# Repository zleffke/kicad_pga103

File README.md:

# kicad_pga103
PGA-103 based low noise amplifier designs.

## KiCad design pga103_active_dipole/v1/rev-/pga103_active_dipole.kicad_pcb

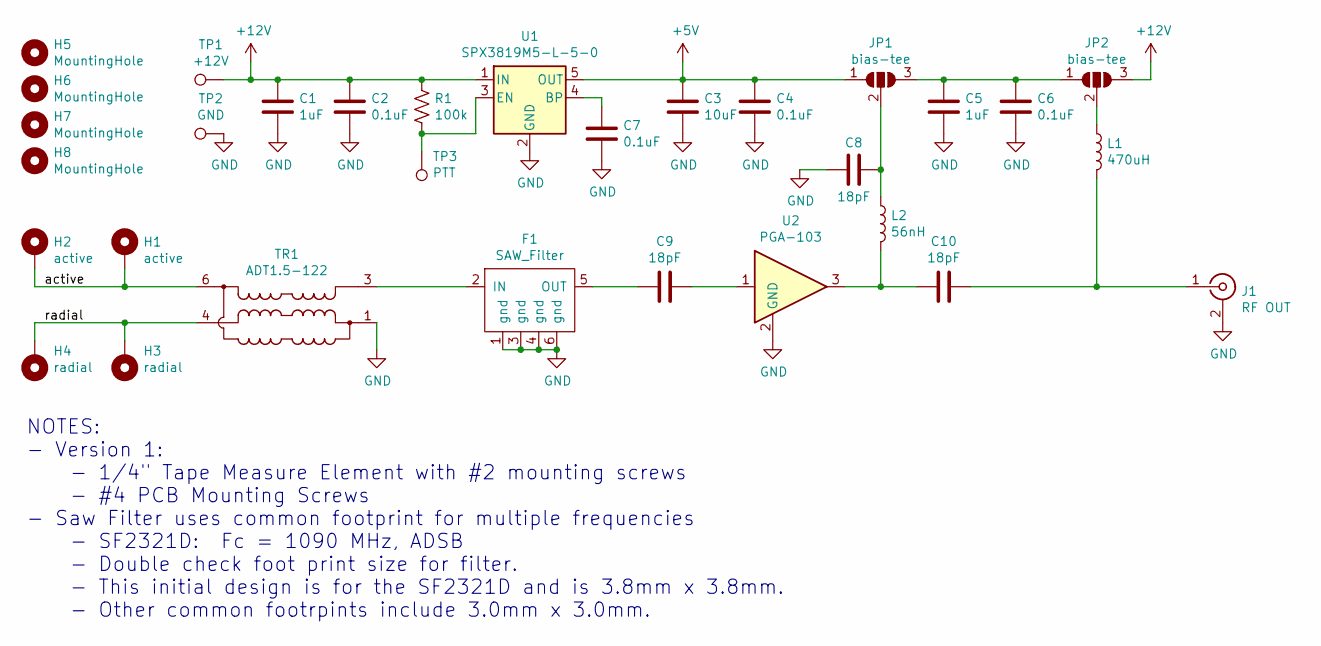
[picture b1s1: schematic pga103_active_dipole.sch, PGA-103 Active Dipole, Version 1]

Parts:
C1, C5: 1uF; 0805
C2, C4, C6, C7: 0.1uF; 0805
C3: 10uF; 0805
C8, C9, C10: 18pF; 0805
F1: SAW_Filter; SM3838-6_3.8mmx3.8mm
H1, H2: active; MountingHole_2.5mm_Pad_Via
H3, H4: radial; MountingHole_2.5mm_Pad_Via
H5, H6, H7, H8: MountingHole; MountingHole_3.2mm_M3
J1: RF OUT; SMA_Samtec_SMA-J-P-X-ST-EM1_EdgeMount
JP1, JP2: bias-tee; SolderJumper-3_P1.3mm_Open_RoundedPad1.0x1.5mm
L1: 470uH; 0805
L2: 56nH; 0805
R1: 100k; 0805
TP1: +12V; TestPoint_Pad_2.0x2.0mm
TP2: GND; TestPoint_Pad_2.0x2.0mm
TP3: PTT; TestPoint_Pad_2.0x2.0mm
TR1: ADT1.5-122; Mini-Circuits_CD542_H2.84mm
U1: SPX3819M5-L-5-0; SOT-23-5
U2: PGA-103; SOT-89-3

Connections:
+5V: C3.1, C4.1, JP1.1 (A), U1.5 (OUT)
+12V: C1.1, C2.1, JP2.3 (B), R1.1, TP1.1, U1.1 (IN)
/active: H1.1, H2.1, TR1.6
/radial: H3.1, H4.1, TR1.4
GND: C1.2, C2.2, C3.2, C4.2, C5.2, C6.2, C7.2, C8.1, F1.1 (gnd), F1.3 (gnd), F1.4 (gnd), F1.6 (gnd), J1.2 (Ext), TP2.1, TR1.1, TR1.2, U1.2 (GND), U2.2 (GND)
unnamed: C5.1, C6.1, JP1.3 (B), JP2.1 (A)
unnamed: C7.1, U1.4 (BP)
unnamed: C8.2, JP1.2 (C), L2.1
unnamed: C9.1, U2.1
unnamed: C9.2, F1.5 (OUT)
unnamed: C10.1, J1.1 (In), L1.2
unnamed: C10.2, L2.2, U2.3
unnamed: F1.2 (IN), TR1.3
unnamed: JP2.2 (C), L1.1
unnamed: R1.2, TP3.1, U1.3 (EN)

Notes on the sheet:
NOTES: - Version 1: - 1/4" Tape Measure Element with #2 mounting screws - #4 PCB Mounting Screws - Saw Filter uses common footprint for multiple frequencies - SF2321D: Fc = 1090 MHz, ADSB - Double check foot print size for filter. - This initial design is for the SF2321D and is 3.8mm x 3.8mm. - Oth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

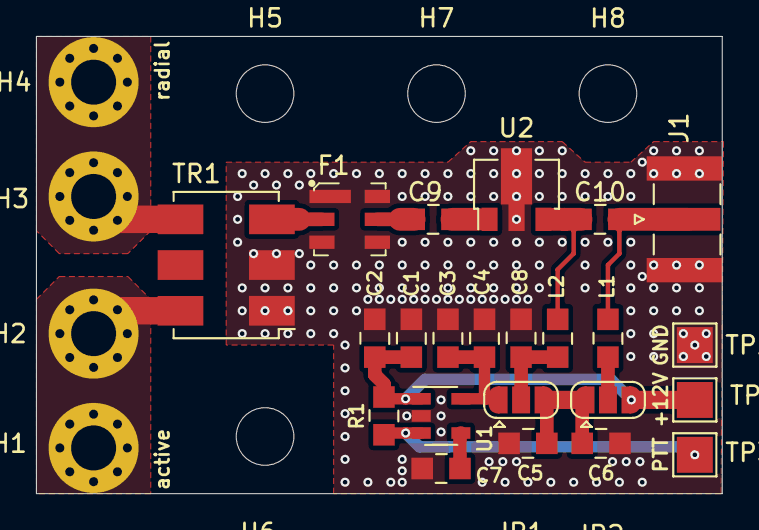
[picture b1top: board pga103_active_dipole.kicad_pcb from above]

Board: 2 copper layers, 38.1 x 25.4 mm, 31 parts (0 on the bottom side), 15 nets.

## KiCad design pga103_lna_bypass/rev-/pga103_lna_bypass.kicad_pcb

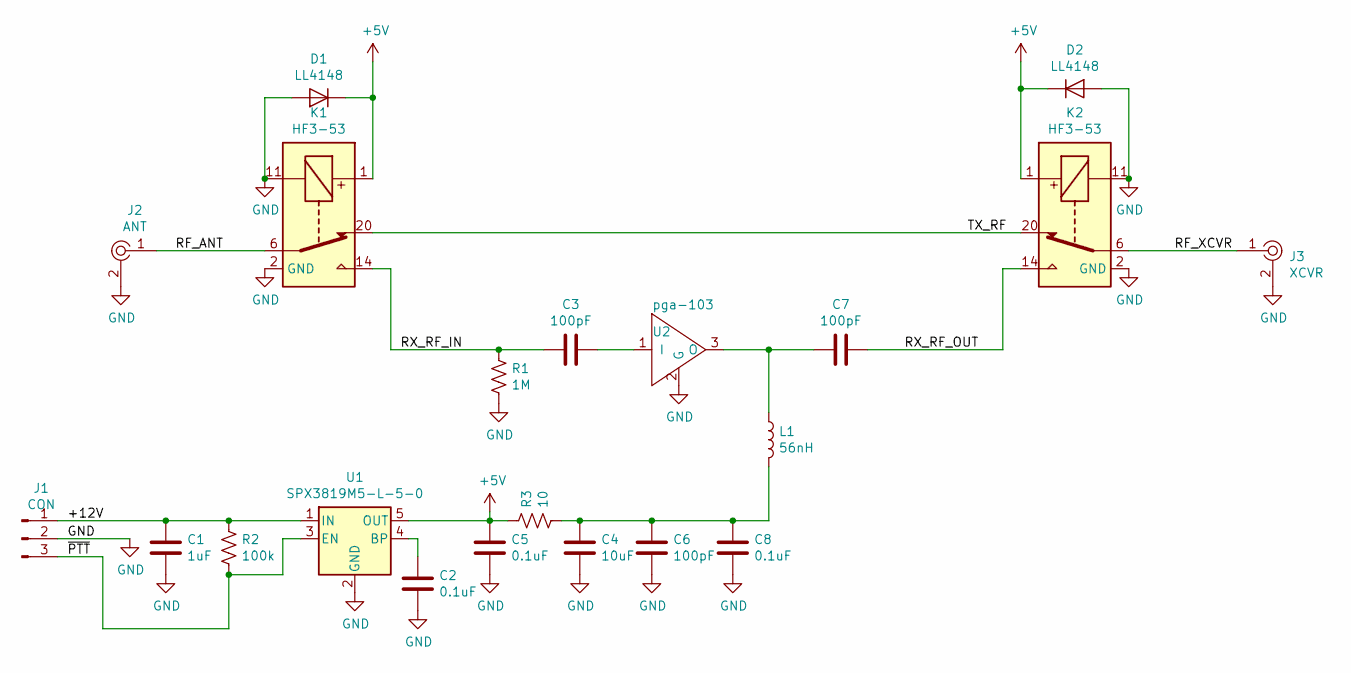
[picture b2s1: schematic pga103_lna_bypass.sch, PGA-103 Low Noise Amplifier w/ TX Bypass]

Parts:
C1: 1uF; 0805
C2, C5, C8: 0.1uF; 0805
C3, C6, C7: 100pF; 0805
C4: 10uF; 0805
D1, D2: LL4148; D_MiniMELF
J1: CON; PinHeader_1x03_P2.54mm_Vertical
J2: ANT; RF_SMA_BoardEdge_142-0701-801; MPN 142-0701-801; Digi-Key_PN J502-ND
J3: XCVR; RF_SMA_BoardEdge_142-0701-801; MPN 142-0701-801; Digi-Key_PN J502-ND
K1, K2: HF3-53; Relay_SPDT_AXICOM_HF3Series_50ohms_Pitch1.27mm
L1: 56nH; 0805
R1: 1M; 0805
R2: 100k; 0805
R3: 10; 0805
U1: SPX3819M5-L-5-0; SOT-23-5
U2: pga-103; SOT-89-3

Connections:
+5V: C5.2, D1.1 (K), D2.1 (K), K1.1, K2.1, R3.2, U1.5 (OUT)
/+12V: C1.2, J1.1, R2.2, U1.1 (IN)
/RF_ANT: J2.1, K1.6
/RF_XCVR: J3.1, K2.6
/RX_RF_IN: C3.2, K1.14, R1.2
/RX_RF_OUT: C7.1, K2.14
/TX_RF: K1.20, K2.20
/~PTT: J1.3, R2.1, U1.3 (EN)
GND: C1.1, C2.1, C4.1, C5.1, C6.1, C8.1, D1.2 (A), D2.2 (A), J1.2, J2.2, J3.2, K1.2 (GND), K1.5 (GND), K1.7 (GND), K1.10 (GND), K1.11, K1.12 (GND), K1.13 (GND), K1.15 (GND), K1.17 (GND), K1.19 (GND), K1.21 (GND), K1.22 (GND), K2.2 (GND), K2.5 (GND), K2.7 (GND), K2.10 (GND), K2.11, K2.12 (GND), K2.13 (GND), K2.15 (GND), K2.17 (GND), K2.19 (GND), K2.21 (GND), K2.22 (GND), R1.1, U1.2 (GND), U2.2 (G)
unnamed: C2.2, U1.4 (BP)
unnamed: C3.1, U2.1 (I)
unnamed: C4.2, C6.2, C8.2, L1.2, R3.1
unnamed: C7.2, L1.1, U2.3 (O)

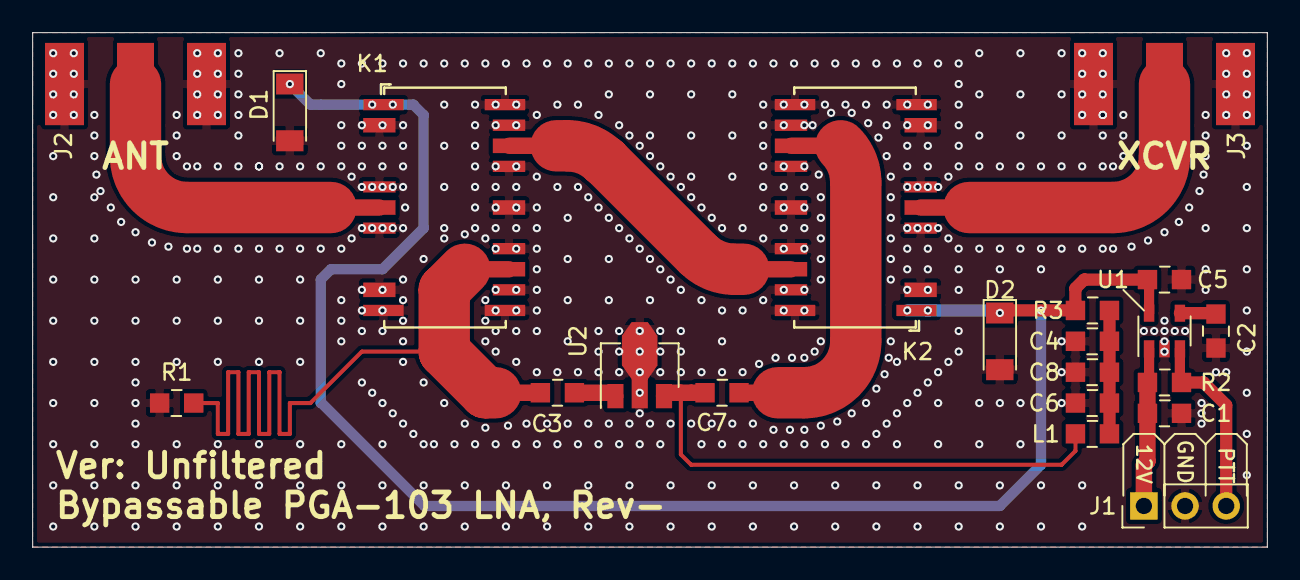
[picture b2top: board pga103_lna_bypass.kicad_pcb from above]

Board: 2 copper layers, 76.2 x 31.8 mm, 21 parts (0 on the bottom side), 13 nets.

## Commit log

2020-11-23 mass commit....not sure the status but might be close to done
2020-12-17 pga-103 active dipole for ADSB reception. This commit submitted to Osh Park.
2021-01-13 updated bias-t values
2021-01-13 adding qucs simulation of bias-t circuit
2021-01-13 updated pdf of schematic
2021-01-13 updated values...470uH to 4.7uH
2021-02-22 commiting everything....
2025-09-17 backing things up

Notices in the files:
pga103_active_dipole/v1/rev-/pga103_active_dipole.sch:
creativecommons.org/licenses/by/4.0
License: CC BY 4.0
